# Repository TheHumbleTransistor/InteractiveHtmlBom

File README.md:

# Interactive HTML BOM plugin for KiCad
## Supports EasyEDA, Eagle, Fusion360 and Allegro PCB designer

This plugin generates a convenient Bill of Materials (BOM) listing with the
ability to visually correlate and easily search for components and their placements
on the PCB. It is particularly useful when hand-soldering a prototype, as it allows
users to quickly find locations of components groups on the board. It is also possible
to reverse lookup the component group by clicking on a footprint on the board drawing.

The plugin utilizes Pcbnew python API to read PCB data and render silkscreen, fab layer,
footprint pads, text, and drawings. BOM table fields and grouping is fully configurable,
additional columns, such as a manufacturer ID, can be added in Schematic editor and
imported either through the netlist file, XML file generated by Eeschema's internal
BOM tool, or from board file itself.

There is an option to include tracks/zones data as well as netlist information allowing
dynamic highlight of nets on the board.

For full description of functionality see [wiki](https://github.com/openscopeproject/InteractiveHtmlBom/wiki).

Generated html page is fully self contained, doesn't need internet connection to work
and can be packaged with documentation of your project or hosted anywhere on the web.

[A demo is worth a thousand words.](https://openscopeproject.org/InteractiveHtmlBomDemo/)

## 3D board view (this fork)

Adds a **3D** button beside F / FB / B. Selecting a BOM row highlights those parts in the 3D
scene and frames the camera on them. When a 3D model is embedded the BOM opens in the 3D view,
unless the browser has saved another choice.

```sh
kicad-cli pcb export glb --include-pads --include-silkscreen --include-soldermask \
    -o board.glb board.kicad_pcb
generate_interactive_bom --glb board.glb board.kicad_pcb
```

Without `--glb` nothing changes: the button is hidden and the output is byte-comparable to
upstream. The `.glb` is embedded, so the result is still one self-contained HTML file.

`--include-silkscreen` is worth the bytes -- reference designators and legends make the 3D view
navigable rather than a field of anonymous grey blocks. Measured on a 170 x 70 mm board:

| glb flags | glb | added to the html |
|---|---|---|
| none | 3.2 MB | 4.3 MB |
| `--include-silkscreen --include-soldermask` | 5.4 MB | 7.2 MB |
| ...`--include-pads` as well (recommended) | 10.6 MB | 14.2 MB |
| ...`--include-tracks` as well | 16.4 MB | 21.9 MB (not worth it) |

three.js adds a further ~2 MB. Pads double the file and are worth it: without them an unplaced
part's land pattern is invisible, which is exactly what an assembler needs to see.

### Z-fighting, and what actually caused it

The artwork layers stipple if you get this wrong. On this board they sit at 1.460 (substrate) /
1.500 (copper) / 1.535 (mask) / 1.545 mm (silk) -- **nothing is coplanar**, the closest pair is
10 um apart. The cause was depth-buffer precision, not coplanarity:

| | near | far | ratio | depth step at the board |
|---|---|---|---|---|
| before | dist/1000 | dist x 10 | 10000 | **17.9 um** -- cannot resolve a 10 um gap |
| after | dist x 0.02 | dist x 4 | 267 | **0.89 um** |

A perspective depth buffer spends most of its precision near the near plane, so an absurd
far/near ratio starves the far end. `setDepthRange()` recomputes it on every frame, because
the camera controls change the viewing distance without going through the fit code. A flat
`polygonOffset` of -1 on artwork faces remains as a cheap guard for boards where faces genuinely
do coincide -- deliberately flat rather than ranked, since large offsets make artwork bleed
through component edges at grazing angles.

### Pin 1

Honours the existing **Highlight first pin** setting (`none` / `all` / `selected`). Each pin-1 pad
gets a 3D marker: a sphere whose bottom sits on top of the part's 3D model, on a cone that runs down
to touch the pad and meets the sphere where their surfaces are tangent. So the marker clears its own
part, with the sphere held between 1.25 mm and 2.5 mm off the board; above that, the 15° outward
lean keeps it off a tall body. A through-hole pin 1 is marked on both faces of the board; on the far
side the sphere clears the leads poking through. A pin-1 marker is plain. A part with no pin 1
(2-4 pads, none named 1, e.g. a diode whose pads are K and A) gets a marker on each pad instead,
with that pad's name printed on the sphere's outer cap, and no pin-1 mark in 2D. The name is fixed
to the marker rather than turning to face the camera; it reads upright with the board's top edge up,
and on bottom-side markers from below. The marker is white at 70 % opacity, with its text opaque.

Every marker's sphere has the same radius, 0.21 mm, so the marker is sized in board millimetres and
grows and shrinks with zoom like the rest of the board. **3D: Pin 1 marker size** in the settings
menu scales it (50–200 %). Markers have their own render pass and light, so the board's dimming
doesn't reach them.

The cone's tip sits on the **board face**, not on the footprint node's origin: the origin is
skewed by any z offset the 3D model carries (`J5`'s is 3.85 mm, which left its mark hovering in
mid-air), and the land pattern is where the mark belongs anyway. It is also drawn for parts the placed
filter is hiding -- an unfitted part is exactly when you need to know which end pin 1 is.

This needs a board-millimetres to model-units mapping, which is the one place the refdes trick
does not reach. It is **solved at load time from every footprint present on both sides**, not
assumed: measured on KiCad 10 the mapping is the identity (board x,y in mm to model x,z in
metres, no offset, no sign flip), and the fit confirms it at a 0.000 mm median residual over 142
footprints. Judge such a fit on the MEDIAN residual, never the worst -- a footprint whose 3D
model carries its own `(offset ...)` is a legitimate outlier, and there were 8 of them. If the
fit fails the markers are disabled with a console warning rather than drawn in the wrong place.

### Silkscreen

The existing **Silkscreen** checkbox governs the 3D view as well as the 2D canvas — no new control;
`silkscreenVisible()` calls into the 3D module the same way `setHighlightPin1()` does.

Silkscreen is identified as the **board-level flat face beyond the mask** on either side, collected
during the pass `tintBoardLayers()` already makes. The board-level part is load-bearing, not
cosmetic: "beyond the front mask" alone means `y > 1.510 mm`, which is *every component on the
board*. Excluding `footprintMeshes` is what makes this the silkscreen rather than the whole
assembly, and the test asserts exactly that — 1154 faces toggle while the component count holds at
7608 in every state.

### The settings menu

All three 3D controls sit together at the end of the view-settings block, between *Offset back
rotation* and *Bom checkboxes*, and each label is prefixed `3D:`.

A **3D view** heading row was tried first and removed: every row in this menu is a bordered box of
the same weight, so a heading reads as just another setting rather than a section title. The prefix
does the grouping work on its own. For the same reason the first 3D row does not get
`menu-label-top` — only the very first row of the whole menu carries a top border, and adding a
divider here would be another visual device of the kind that did not work.

The **Footprint column is hidden by default** (`hiddenColumns` in `initDefaults()`). Default only:
a stored preference wins, the existing `.filter(e => fields.includes(e))` drops it harmlessly on a
BOM with no such column, and the column stays available to re-enable in the column menu.

### Zoom on select

A **3D: Zoom on select** slider in the settings menu. It works like cropping: the percentage is how
much of the board is cropped out of view, centred on the selected parts.

- **0 % (default):** the camera doesn't move; selecting a row only highlights it.
- **10 %** shows about 90 % of the board's area, **50 %** about half, and so on up to **100 %**.
- However high the setting, the camera never gets so close that the selection fills more than 20 %
  of the view, so there is always some board around it for context. It never zooms out past the
  whole board either, so deselecting returns to the whole-board view.

The zoom is absolute, worked out fresh on every selection, so selecting the same row again doesn't
zoom further. The view direction is kept; only the target and distance change. A new value applies
on the next selection.

### Free rotation

The board turns freely in every direction, over the top and underneath, with no stop at the poles:
the view uses three.js's TrackballControls rather than OrbitControls, which keeps a fixed "up"
direction. Left-drag rotates, the wheel zooms and right-drag pans, as before.

### Flip to the selection

Selecting parts that are all on the side facing away from the camera turns the board over, like
turning a page: over half a second the camera rotates half a turn about the line on the board that
looks vertical on screen, keeping its distance. The result is what you'd see after flipping the
board over by hand. If any selected part is on the visible side, the view stays put. The key light
follows the camera to whichever side it is on, so the underside is lit like the top.

### Deselecting

Upstream iBOM has no way to clear a selection: `clearHighlightedFootprints()` is only reachable by
switching BOM mode, and `createRowHighlightHandler()` returns early on the already-selected row.
Tolerable for a highlight tint on the 2D canvas; not for the 3D view, where a selection also dims the
board and holds the camera. This fork adds two ways out:

- **Escape** — works in either mode, hooked into the existing `document.onkeydown` switch.
- **Double-clicking the 3D view** — no raycast; any double-click means "get me out of this",
  whether it lands on a part or on bare board. The camera controls bind no `dblclick` of their own and a
  double-click involves no drag, so the camera is untouched.
- **Clicking the selected row again** — click mode only. In hover mode (the default, when
  *Highlight row only on click* is off) that same handler is bound to `onmousemove` and fires on every
  movement within the row, so toggling there would strobe.

Worth knowing: with the default hover mode the selection follows the mouse across the table and
never clears on its own. Turning on *Highlight row only on click* makes selection deliberate.

### 3D: Board mask

A 0–100 % slider in the settings menu, **75 % by default**. While a row is selected it darkens the board
and every unselected component, leaving the green highlighted parts bright — useful on a dense board,
and especially at 0 % auto-zoom where the camera no longer flies to the selection.

**Implemented by turning the lights down, not by recolouring materials.** The highlight is emissive,
and emissive is added independently of scene lighting, so scaling `scene.environmentIntensity` and
the key light darkens everything *except* the selection. Two lines, against cloning and restoring
~36 materials across 7608 meshes. Measured inside the 3D pane:

| slider | `environmentIntensity` | board (non-highlight) | highlight, mean R |
|---|---|---|---|
| 0 % | 0.62 | 92.3 | 174.1 |
| 50 % | 0.341 | 74.9 | 200.6 |
| 100 % | 0.062 | **34.7** | **214.5** |

`DIM_FLOOR` is the light scale at 100 %; the slider lerps between 1 and it.

The selected part's *diffuse* darkens along with everything else, so its emissive is raised while
dimming (`HIGHLIGHT_EMISSIVE_DIM`) or it reads as a muddy dark part with a red tinge rather than a
clean red one. `DIM_FACTOR` controls how far down everything else goes.

Only active while something is selected — deselecting restores the lights, verified. Pin-1 markers are
drawn in their own pass with their own lighting, so they stay bright on the dimmed board;
deliberate, they are a marker rather than scenery.

### Only show placed parts

A **3D: only show placed parts** checkbox in the settings menu, on by default. With it on, the 3D view shows
only the parts ticked in the BOM's *Placed* column -- so the board fills in as you assemble it,
and at a glance you see what the half-built board in front of you should look like.

**DNP parts are hidden in 3D until they are ticked Placed**, whether or not this is on.
Selecting one reveals it with a red highlight instead of the usual green. A DNP part that has
been ticked Placed is shown tinted red. A
part counts as DNP if `--dnp-field` marks it or KiCad's own DNP flag (`kicad_dnp`) is set.

**Land patterns stay visible, and selecting an unplaced row reveals that part** — fully opaque,
exactly as a placed part looks — so you can see the shape of the thing you are about to fit.

It was briefly revealed as a *translucent* ghost instead, which rendered as a see-through tangle of
red edges. The culprit was the `depthWrite = false` that the transparency required: it also stops
the part's own faces occluding **each other**, so every back face and interior surface showed
through the front. No opacity value fixes that — the geometry is self-overlapping and unsorted.
Opaque is both correct and less code.

Nothing is overlaid on the components themselves -- no tint, no shading, no transparency -- so a
populated board renders as it really looks and the green highlight is the only thing distinguishing
a selection. Verified by material inspection: of 7608 component meshes, 0 are transparent, 0
share a tinted material and 0 carry a polygon offset. Both matter for the actual workflow: you need to see where a part goes,
and what it looks like, *before* you can fit it and tick it off.

**Pads and silkscreen are board-level, not children of the footprint node** -- so hiding a part
is simply `node.visible = false` and the land pattern stays put. Counted on this board:

| plane (mm) | under footprints | board-level | what |
|---|---|---|---|
| 1.545 | **371** | 0 | component bottom faces |
| 1.535 | 0 | 1153 | silkscreen |
| 1.510 | 0 | 1 | top soldermask, one full-board mesh |
| 1.500 | 0 | 582 | top copper |
| 1.460 | 0 | 500 | substrate, top face |
| 0.000 | 0 | 84 | substrate, bottom face |
| −0.040 | 0 | 166 | bottom copper |
| −0.050 | 0 | 1 | bottom soldermask, one full-board mesh |

Earlier versions tried to split each footprint into "artwork" and "body" by height, on the belief
that pads were inside it. They are not, and every height rule tried caught component geometry
instead -- a +/-0.2 mm window took TSSOP leads at 1.58-1.70 mm, and "a plane shared by most
footprints" took the 1.545 mm bottom faces, which is true of every SMD's underside. Hiding a part
left a flat cross-section of it welded to the board. **Measure which meshes are actually inside
the node before designing a rule around it.**

### DNP parts

DNP parts are marked so an assembler can't miss them. Every badge below explains itself on hover,
and clicking it shows the same text, which also works on touchscreens:

- **BOM:** DNP refs are red and struck through, and a row that is entirely DNP is tinted red with lightened text and a red stripe that stays when the row is
  selected.
- **2D and 3D:** a red cross over each DNP footprint, shown while the **DNP markers** setting is
  on (the default). A selected DNP part is highlighted red in both views instead of green. In 3D
  the cross sits on the bare land pattern, and the part is tinted red once it is ticked Placed.
- **Checkbox progress** (e.g. *Placed 0/140*) leaves DNP parts out of the total.
- **Grouping** always puts DNP parts in their own row, whatever `--group-fields` says.
- **Ticking Placed** (or whichever column `--mark-when-checked` names) on a DNP row asks for
  confirmation first. The operator can still go ahead.
- Hovering a red, struck-through reference explains it ("DNP = Do Not Populate").
- KiCad's DNP column (`kicad_dnp`) is headed **DNP** and shows a red **DNP** badge on DNP rows. It
  is hidden by default (the column menu brings it back), and left out entirely on a board with no
  DNP parts in the BOM.

A part counts as DNP if `--dnp-field` marks it or KiCad's DNP flag (`kicad_dnp`) is set. A part
whose *value* says "DNP" (as a word, any case) is treated as DNP too, and its value cell gets a
yellow **WARNING** badge: DNP belongs in KiCad's DNP property, not the value.

### Lighting

**Every component material KiCad exports is `metalness: 1`** -- all 7608 meshes on this board.
A fully metallic surface has no diffuse response, so with only lights and nothing to reflect it
can only render dark: a connector housing whose material is pure white measured RGB ~120, i.e.
grey. Raising light intensities does not help, because a metal barely responds to a light at all.

The fix is image-based lighting -- `RoomEnvironment` through `PMREMGenerator`, giving those metals
a full hemisphere to reflect -- plus one soft directional light so shapes still read. A white part
now renders ~210 from any angle.

**Tone mapping is not cosmetic here.** Without it, values above 1.0 clip and a white part becomes a
flat 255 across its whole face, losing all shape. `NeutralToneMapping` (Khronos PBR Neutral) rolls
highlights off while holding colours where they are; it exists for product visualisation, which is
exactly this job. ACES works too but shifts hue. Measured on the same white part: **0.06 % of
pixels clipped**, against a blown-out face before.

`ENV_INTENSITY`, `KEY_INTENSITY` and `TONE_EXPOSURE` are at the top of `ibom3d.js`. Note that
changing them changes the *board* too -- `MASK_COLOR` and `COPPER_COLOR` were both retuned darker
once IBL raised the overall exposure.

### Layer colours

KiCad **does** honour the stackup for silkscreen -- this board declares white silk and the GLB
carries `#f5f5f5` -- but gives copper a flat `#808080`, which is nobody's idea of copper. Both
soldermask and copper are therefore tinted, and the mask is made slightly translucent so the
copper beneath reads through. A green board is what reads as "a PCB" on screen whatever the real
stackup says; set `MASK_COLOR = null` to keep the exported colour instead. `MASK_COLOR`,
`MASK_OPACITY`, `COPPER_COLOR`, `COPPER_METALNESS` and `COPPER_ROUGHNESS` are at the top of
`ibom3d.js`.

Copper also needs its **PBR properties** overridden, not just its colour. KiCad exports it as
`metalness 1 / roughness 0.4`, and a fully metallic surface has no diffuse term -- with no
environment map to reflect, it is black except where a light happens to catch it. Measured over
the copper-toned pixels of an isolated render:

| | copper pixels | mean RGB |
|---|---|---|
| metalness 1, top-down | 5367 | (140, 121, 82) |
| metalness 1, shallow | **0 -- none** | copper vanishes |
| metalness 0, top-down | 5730 | (225, 197, 138) |
| metalness 0, shallow | 4050 | (221, 192, 134) |

At `metalness 0 / roughness 0.7` the colour is within ~2 % across viewing angles.

Identify the layers by **area**, not mesh count or height rank: the full-board planes on a side are
the substrate face and the mask, and copper is the busiest plane between them. Ranking from the top
puts the tint on the silkscreen, and a "more than 20 meshes" filter discards the soldermask
outright, it being a single mesh. For the same reason `findBoardFaces()` cannot look for a
substrate *solid*: the board is flat faces too.

**Both faces are tinted**, by `identifySide()` run once per side. The rule generalises with one
substitution: the mask is the **outermost** full-board plane on its side — highest at the front,
lowest at the back — with the substrate the inner one. The back was skipped for a while
(`tintBoardLayers()` opened with `if (y < mid) return`), which left the bottom mask and copper in
KiCad's greys and reading as absent:

| plane | before | after |
|---|---|---|
| −0.050 bottom mask | `#373737` grey | `#185230` green, α 0.80 |
| −0.040 bottom copper | `#bababa` grey, **metalness 1** | `#c3903e` gold, metalness 0 |

Note the bottom copper arrived at `metalness 1`, so it had the black-at-grazing-angles problem too;
routing it through the same tint pass fixes that as well.

It rides iBOM's own `CHECKBOX_CHANGE_EVENT`, so no checkbox bookkeeping is patched. It follows
whichever column `--mark-when-checked` names, defaulting to `Placed`.

**How the mapping works.** KiCad's GLB export names every scene node for its reference
designator, so a BOM row finds its geometry by name -- no coordinate transform, no lookup table
to keep in sync, and it survives the board moving underneath it. Parts with no 3D model are
skipped and counted in a corner note. On this project's board 142 of 178 footprints have named
nodes, and the 36 that do not are exactly the `TP*`/`MH*`/`FID*`/logo set that iBOM already
excludes from the BOM -- so no BOM row is ever unmatched.

**Design notes**, mostly so they are not re-litigated:

- three.js r169 is vendored **unmodified** under `web/three/` (MIT, `LICENSE` included) and
  inlined as `data:` URIs in an import map. ES modules cannot be concatenated and three.js has
  shipped no UMD build since r160, so something must resolve the bare `three` specifier inside
  an inlined `<script type=module>`. A `data:` import map does it **with no bundler**, which
  keeps the single-file property and adds no Node toolchain.
- The one build-time edit: `GLTFLoader` imports `BufferGeometryUtils` by *relative* path, and a
  relative specifier cannot resolve when the importing module is itself a `data:` URI. That
  single import is rewritten to a bare specifier in `core/ibom.py`; the vendored file on disk
  stays pristine.
- KiCad exports GLB in **metres**, not millimetres.
- `tests/check_3d.py` screenshots a generated file in headless Chromium (software WebGL, no GPU
  needed). It is the only thing that can catch a blank 3D pane, which is otherwise silent.

### Demo board

`demo/` holds a small KiCad 10 board for trying changes without another project. R4 and C5 are DNP
through KiCad's DNP property, and R7 only through its value ("DNP"), which shows the WARNING badge.
R6 and C6 are on the back. D1's pads are named K and A rather than numbered, which shows how a part
with no pin 1 is labelled. Every part has a Manufacturer and MPN. Its 3D models are copied into
`demo/3dmodels/`, so it builds without KiCad's model library.

```sh
demo/build.sh                 # -> demo/out/ibom-demo.html
```

It needs `kicad-cli` and a python that can `import pcbnew` (`$PYTHON`, default `/usr/bin/python3`).
CI runs the same script for every pull request and for pushes to `master`, and keeps the result as
the `ibom-demo.html` artifact (unzipped) for 30 days. On a pull request, each build
posts a new comment linking its demo; a newer push cancels a build still in progress, so only the
latest commit gets one. Pushing a `v*` tag also attaches the demo to that tag's release as
`ibom-demo-<tag>.html`, creating the release if there isn't one.

### Mounting type

A **Mounting Type** column, visible by default, shows **SMT** (grey rounded rectangle, a pad) or
**TH** (grey ring, an annular ring). Sort on it to group the two, or type `smt` / `th` in the
filter box. Hovering the header or a value explains the acronym.

The value comes from KiCad's footprint type (Footprint Properties, *SMD* or *Through hole*). A
footprint left *Unspecified*, or a board from another EDA tool, counts as TH if any of its pads is
through-hole and SMT otherwise.

### Default columns

Without `--show-fields` the BOM shows **Manufacturer** and **MPN** columns alongside Value and
Footprint, even on a board where no part sets them. Grouping still defaults to Value and Footprint.

### Side, and sorting by more than one column

A **Side** column, visible by default, shows **Top** or **Bottom**. While it is shown, a group with
parts on both sides is split into a top row and a bottom row; hide the column and they merge back.

**Shift+click** a column header to add it as a further sort key, e.g. Side then Mounting Type. A
small number on each sorted header shows its priority. A plain click sorts by that column alone.

### Polarized parts and pin 1

Each part is classified **Yes**, **No** or **Unknown** for whether its orientation matters. The
classification is shown in a **Polarized** column, hidden by default (the column menu shows it).

- **No** requires evidence from the part's schematic symbol and none to the contrary: a two-pad
  R, C, L, FB or F whose Description (copied from the symbol) reads "Resistor", "Unpolarized
  capacitor", "Inductor", "Ferrite bead", "Fuse" or mentions ceramic, or whose symbol footprint
  filters are `R_*`, `C_*`, `L_*` and the like, **and** whose footprint silkscreen is symmetric
  about both of its axes (a "+", cathode band or pin-1 dot breaks that). The footprint alone never
  makes a part No, since polarized capacitors are often placed on plain, symmetric `C_` footprints.
- **Yes**: a polarity signal (`CP_` footprint or filter, "Polarized capacitor", a diode or LED), or
  more than two pins.
- **Unknown**: everything else, including conflicting evidence (a bidirectional TVS diode, an
  inductor whose footprint marks pin 1), no silkscreen, or no symbol fields at all.

**Omit pin-1 marker on bidirectional parts**, on by default, hides the pin-1 marks of parts classified No,
in both the 2D and 3D views. Turn it off to mark every part again. Yes and Unknown parts always keep
their marks.

### Sound Effect on Placed

Off by default. With it on, ticking a line's Placed box plays a clay block being set down for each
of its parts, stepping up in pitch as the stack grows, up to 10. Lines ticked during a run, or
within half a second after it, add to the same run. Placing the last part plays a short fanfare.
Unticking is silent. The sound is synthesised in the browser, so the BOM carries no audio files.

## Installation and Usage

See [project wiki](https://github.com/openscopeproject/InteractiveHtmlBom/wiki/Installation) for instructions.

## License and credits

Plugin code is licensed under MIT license, see `LICENSE` for more info.

Html page uses [Split.js](https://github.com/nathancahill/Split.js),
[PEP.js](https://github.com/jquery/PEP) and (stripped down)
[lz-string.js](https://github.com/pieroxy/lz-string) libraries that get embedded into
generated bom page.

`units.py` is borrowed from [KiBom](https://github.com/SchrodingersGat/KiBoM)
plugin (MIT license).

`svgpath.py` is heavily based on
[svgpathtools](https://github.com/mathandy/svgpathtools) module (MIT license).

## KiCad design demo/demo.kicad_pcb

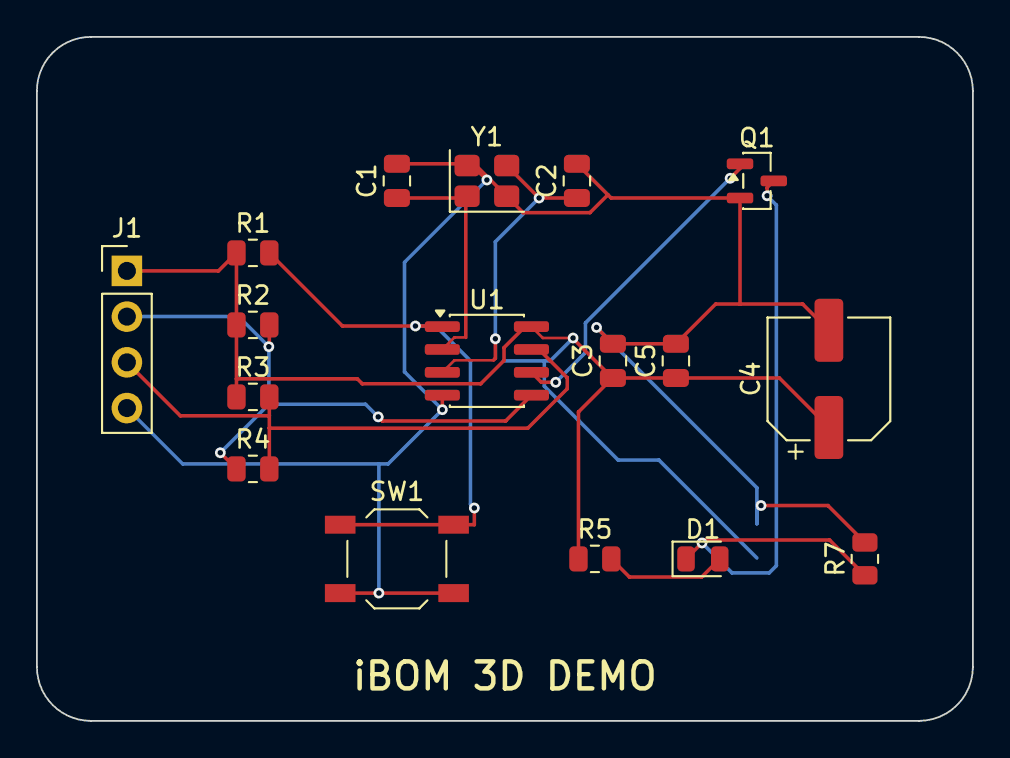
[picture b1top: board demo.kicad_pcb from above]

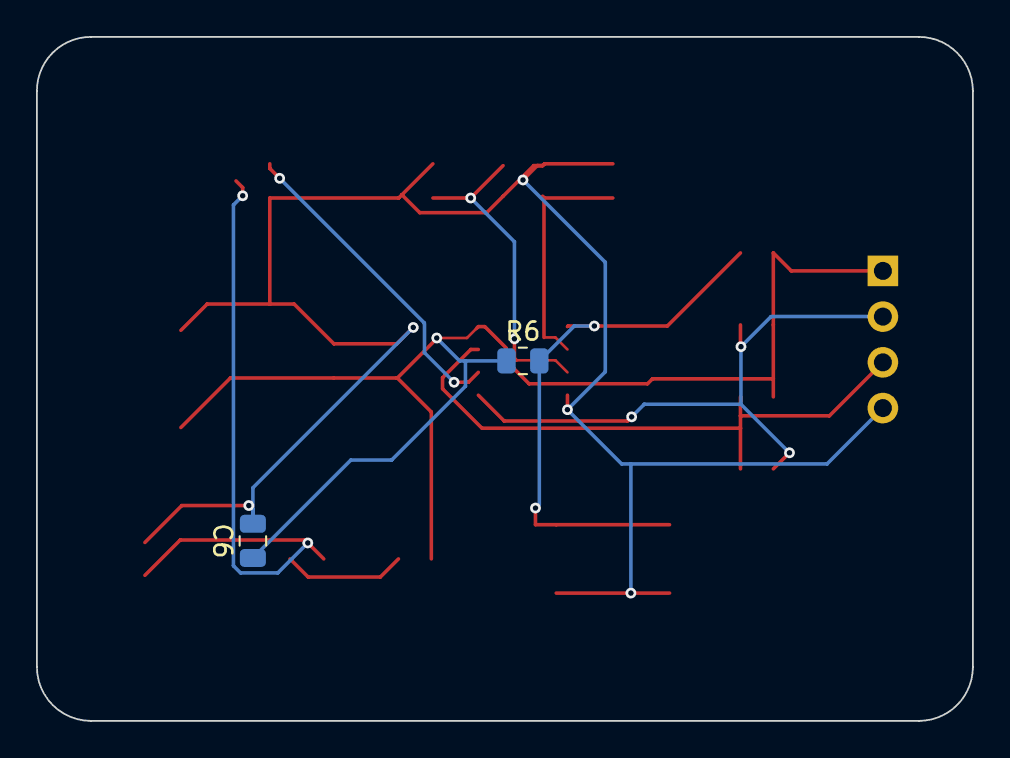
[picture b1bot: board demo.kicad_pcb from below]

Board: 2 copper layers, 52.0 x 38.0 mm, 19 parts (2 on the bottom side), 10 nets.

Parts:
C1, C2: 22pF; C_0805_2012Metric
C3, C6: 100nF; C_0805_2012Metric
C4: 47uF; CP_Elec_6.3x5.8
C5: 1uF; C_0805_2012Metric
D1: Green; LED_0805_2012Metric
J1: Conn_01x04; PinHeader_1x04_P2.54mm_Vertical
Q1: BSS138; SOT-23
R1, R6: 10k; R_0805_2012Metric
R2, R3: 4.7k; R_0805_2012Metric
R4: 0R; R_0805_2012Metric
R5: 1k; R_0805_2012Metric
R7: DNP; R_0805_2012Metric
SW1: Reset; SW_SPST_TL3342
U1: ATtiny85; SOIC-8_3.9x4.9mm_P1.27mm
Y1: 16MHz; Crystal_SMD_3225-4Pin_3.2x2.5mm

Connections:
GND: C1.2, C2.2, C3.2, C4.2, C5.2, C6.2, J1.4, Q1.2, R7.2, SW1.2, U1.4, Y1.2, Y1.4
LED: Q1.1, U1.6
LED_A: D1.A, R5.2
LED_K: D1.K, Q1.3, R7.1
RST: R1.2, R6.2, SW1.1, U1.1
SCL: J1.3, R3.2, R4.2, U1.7
SDA: J1.2, R2.2, R4.1, U1.5
VCC: C3.1, C4.1, C5.1, C6.1, J1.1, R1.1, R2.1, R3.1, R5.1, R6.1, U1.8
XTAL1: C1.1, U1.2, Y1.1
XTAL2: C2.1, U1.3, Y1.3
